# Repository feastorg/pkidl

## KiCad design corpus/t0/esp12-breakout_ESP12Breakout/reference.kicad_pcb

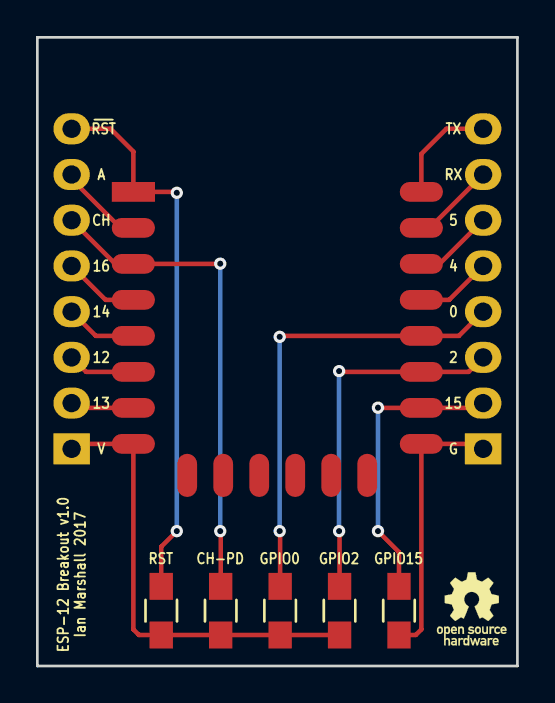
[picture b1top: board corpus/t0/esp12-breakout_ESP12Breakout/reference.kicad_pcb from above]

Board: 2 copper layers, 26.7 x 34.9 mm, 8 parts (0 on the bottom side), 16 nets.

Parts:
P1, P2: CONN_01X08; Socket_Strip_Straight_1x08
R1, R2, R3, R4, R5: 10k; R_0805_HandSoldering
U1: ESP-12E

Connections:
GND: P2.1, R5.1, U1.15
unnamed: P1.2, U1.7
unnamed: P1.3, U1.6
unnamed: P1.4, U1.5
unnamed: P1.5, U1.4
unnamed: P1.6, R2.2, U1.3
unnamed: P1.7, U1.2
unnamed: P1.8, R1.2, U1.1
unnamed: P2.2, R5.2, U1.16
unnamed: P2.3, R4.2, U1.17
unnamed: P2.4, R3.2, U1.18
unnamed: P2.5, U1.19
unnamed: P2.6, U1.20
unnamed: P2.7, U1.21
unnamed: P2.8, U1.22
VCC: P1.1, R1.1, R2.1, R3.1, R4.1, U1.8

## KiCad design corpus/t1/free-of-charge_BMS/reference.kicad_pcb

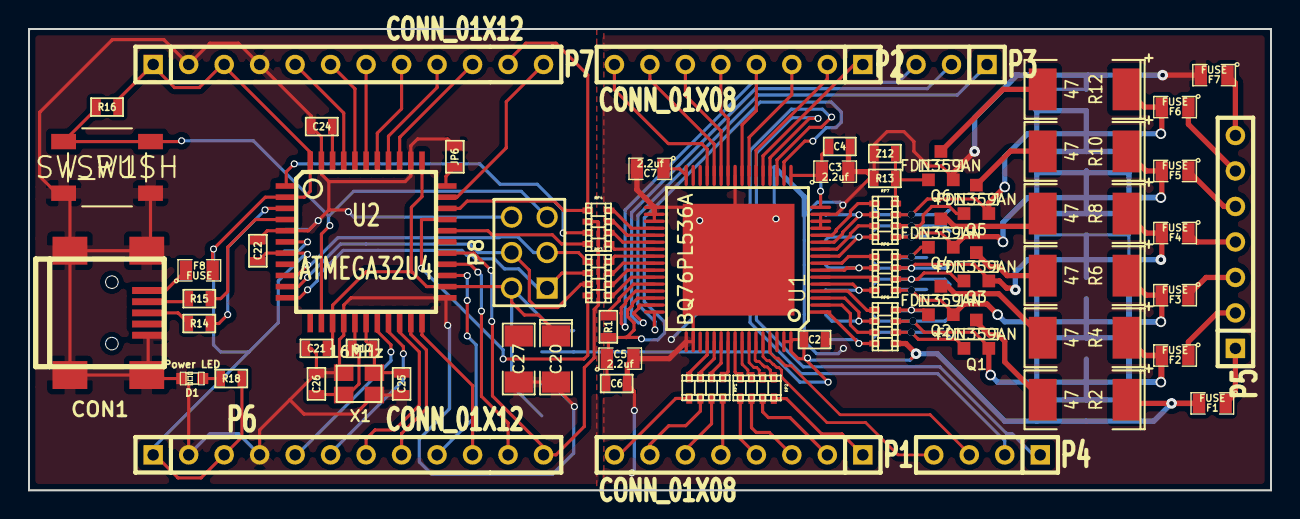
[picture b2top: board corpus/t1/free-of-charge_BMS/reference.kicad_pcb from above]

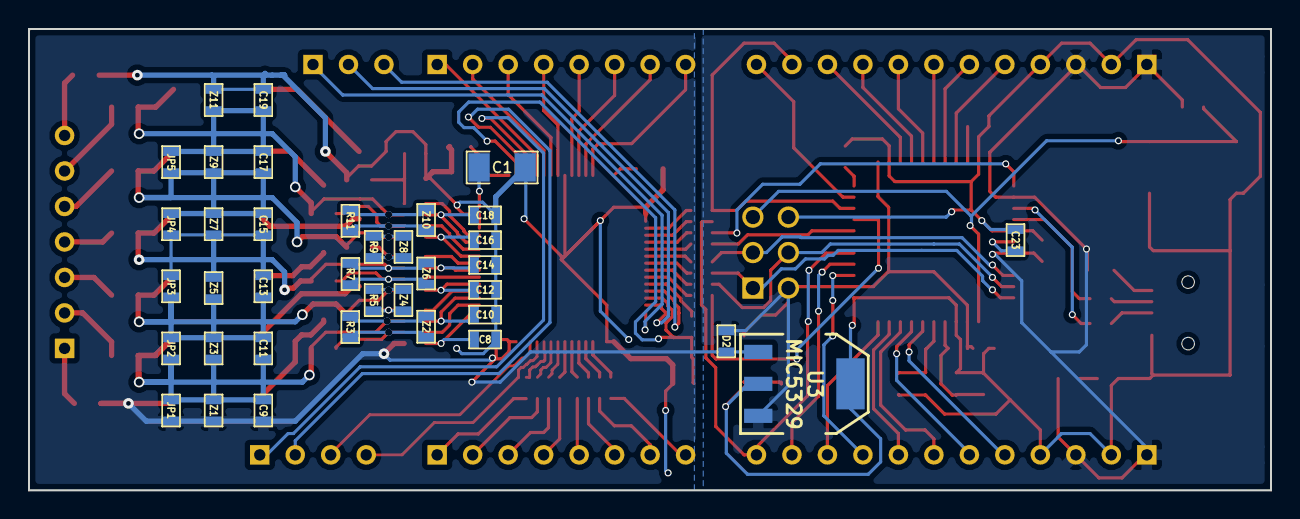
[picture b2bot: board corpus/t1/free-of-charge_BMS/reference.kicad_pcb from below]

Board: 2 copper layers, 88.9 x 33.0 mm, 100 parts (37 on the bottom side), 118 nets.

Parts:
C1, C27: 10uf; SM1206
C2, C4, C6, C8, C9, C10, C11, C12, C13, C14, C15, C16, C17, C18, C19, C21, C22, C24: 0.1uf; SM0603
C3, C5, C7: 2.2uf; SM0805
C20: 10uf; SM1206POL
C23: 1uf; SM0603
C25, C26: 20pf; SM0603
CON1: USB-MINI-B; USB_MINI_B
D1: Power LED; LED-0603
D2: DIODE; SM0603
F1, F2, F3, F4, F5, F6, F7, F8: FUSE; SM0805
JP1, JP2, JP3, JP4, JP5, JP6: JUMPER; SM0603
P1, P2: CONN_01X08; SIL-8
P3: CONN_01X03; SIL-3
P4: CONN_01X04; SIL-4
P5: CONN_01X07; SIL-7
P6, P7: CONN_01X12; SIL-12
P8: CONN_02X03; pin_array_3x2
Q1, Q2, Q3, Q4, Q5, Q6: FDN359AN; SOT23GDS
R1: 100k; SM0603
R2, R4, R6, R8, R10, R12: 47; SM2512
R3, R5, R7, R9, R11, R13: 1M 1%; SM0603
R14, R15: 22; SM0603
R16: 10k; SM0603
R17: 1M; SM0603
R18: 1k; SM0603
RP1, RP2, RP3, RP4: R_PACK4; r_cat16-4
RP5, RP6, RP7: 1k; r_cat16-4
SW1: SW_PUSH; SW
U1: BQ76PL536A; HTQFP_64
U2: ATMEGA32U4; TQFP44
U3: MIC5329; SOT223
X1: 16MHz; crystal_FA238-TSX3225
Z1, Z2, Z3, Z4, Z5, Z6, Z7, Z8, Z9, Z10, Z11, Z12: ZENER; SM0603

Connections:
+5V: C20.1, C21.1, C22.1, D2.1, F8.2, P6.1, P6.3, P7.1, P7.3, P8.2, R16.1, R18.2, U2.2, U2.7, U2.14, U2.24, U2.34, U2.44, U3.3
+BATT: C2.1, C9.1, D2.2, F1.2, JP1.1, R2.1, RP5.1, U1.63, U1.64, U3.1, Z1.2
/CellBallance/C0: F7.1, P5.7
/CellBallance/C1: F6.1, P5.6
/CellBallance/C2: F5.1, P5.5
/CellBallance/C3: F4.1, P5.4
/CellBallance/C4: F3.1, P5.3
/CellBallance/C5: F2.1, P5.2
/CellBallance/C6: F1.1, P5.1
/CellBallance/CB1: RP7.5, U1.12
/CellBallance/CB2: RP7.7, U1.10
/CellBallance/CB3: RP6.5, U1.8
/CellBallance/CB4: RP6.7, U1.6
/CellBallance/CB5: RP5.5, U1.4
/CellBallance/CB6: RP5.7, U1.2
/CellBallance/VC1: C18.2, RP7.6, U1.11
/CellBallance/VC2: C16.2, RP7.8, U1.9
/CellBallance/VC3: C14.2, RP6.6, U1.7
/CellBallance/VC4: C12.2, RP6.8, U1.5
/CellBallance/VC5: C10.2, RP5.6, U1.3
/CellBallance/VC6: C8.2, RP5.8, U1.1
/LDOA: C3.1, C4.1, U1.17
/LDOD: C5.1, C6.1, R1.2, U1.18, U1.46
/REG50: C7.1, U1.32
/VREF: C1.1, U1.16
/atmega32u4/A0: P7.10, U2.36
/atmega32u4/A1: P7.9, U2.37
/atmega32u4/A2: P7.8, U2.38
/atmega32u4/A3: P7.7, U2.39
/atmega32u4/A4: P7.6, U2.40
/atmega32u4/A5: P7.5, U2.41
/atmega32u4/ALERT_H: RP4.7, U2.1
/atmega32u4/AREF: C24.1, U2.42
/atmega32u4/CONV_H: P7.11, RP4.5, U2.31
/atmega32u4/CS_H: RP3.8, U2.30
/atmega32u4/D0/RX: P6.7, U2.20
/atmega32u4/D1/TX: P6.8, U2.21
/atmega32u4/D2/SDA: P6.6, U2.19
/atmega32u4/D3/SCL: P6.5, U2.18
/atmega32u4/D4: P6.9, U2.25
/atmega32u4/DRDY_H: P6.12, RP4.6, U2.27
/atmega32u4/FAULT_H: RP4.8, U2.29
/atmega32u4/HWB: JP6.1, U2.33
/atmega32u4/IO12: P6.11, U2.26
/atmega32u4/IO13*: P7.12, U2.32
/atmega32u4/RST: P8.5, R16.2, SW1.2, U2.13
/atmega32u4/SCLK_H: P8.3, RP3.5, U2.9
/atmega32u4/SDI_H: P8.4, RP3.7, U2.10
/atmega32u4/SDO_H: P8.1, RP3.6, U2.11
/atmega32u4/TXLED: P6.10, U2.22
/atmega32u4/UCAP: C23.1, U2.6
GND: C20.2, C21.2, C22.2, C23.2, C24.2, C25.2, C26.2, C27.2, CON1.5, CON1.6, CON1.7, CON1.8, CON1.9, D1.2, JP6.2, P6.2, P6.4, P7.2, P7.4, P8.6, SW1.1, U2.5, U2.15, U2.23, U2.35, U2.43, U3.2, U3.4, X1.3
unnamed: P2.1, U1.21
unnamed: P2.2, U1.22
unnamed: P2.3, U1.23
unnamed: P2.4, U1.24
unnamed: P2.5, U1.26
unnamed: P2.6, U1.27
unnamed: P1.3, RP2.2
unnamed: P1.2, RP2.3
unnamed: P1.1, RP2.4
unnamed: P1.4, RP2.1
unnamed: P2.7, U1.28
unnamed: P2.8, U1.29
unnamed: P1.5, RP1.4
unnamed: P1.6, RP1.3
unnamed: P1.7, RP1.2
unnamed: P1.8, RP1.1
unnamed: P3.2, U1.47
unnamed: RP1.8, U1.52
unnamed: RP1.7, U1.53
unnamed: RP1.6, U1.54
unnamed: RP1.5, U1.55
unnamed: P3.3, U1.45
unnamed: P3.1, U1.48
unnamed: P4.4, U1.60
unnamed: P4.3, U1.61
unnamed: P4.2, U1.19
unnamed: RP3.4, U1.40
unnamed: RP3.3, U1.41
unnamed: RP3.2, U1.42
unnamed: RP3.1, U1.43
unnamed: P4.1, U1.20
unnamed: RP4.4, U1.36
unnamed: RP4.3, U1.37
unnamed: RP4.2, U1.38
unnamed: RP4.1, U1.39
unnamed: RP2.8, U1.56
unnamed: RP2.7, U1.57
unnamed: RP2.6, U1.58
unnamed: RP2.5, U1.59
unnamed: R1.1, U1.44
unnamed: Q1.G, R3.1, RP5.2, Z2.2
unnamed: Q1.D, R2.2
unnamed: Q2.D, R4.2
unnamed: Q6.G, R13.1, RP7.4, Z12.2
unnamed: Q4.G, R9.1, RP6.4, Z8.2
unnamed: Q5.D, R10.2
unnamed: Q5.G, R11.1, RP7.2, Z10.2
unnamed: Q3.G, R7.1, RP6.2, Z6.2
unnamed: C13.2, C15.1, F4.2, JP3.2, JP4.1, Q3.S, R7.2, R8.1, RP6.3, Z5.1, Z6.1, Z7.2
unnamed: Q2.G, R5.1, RP5.4, Z4.2
unnamed: C15.2, C17.1, F5.2, JP4.2, JP5.1, Q4.S, R9.2, R10.1, RP7.1, Z7.1, Z8.1, Z9.2
unnamed: C17.2, C19.1, F6.2, JP5.2, Q5.S, R11.2, R12.1, RP7.3, Z9.1, Z10.1, Z11.2
unnamed: Q6.D, R12.2
unnamed: C11.2, C13.1, F3.2, JP2.2, JP3.1, Q2.S, R5.2, R6.1, RP6.1, Z3.1, Z4.1, Z5.2
unnamed: C9.2, C11.1, F2.2, JP1.2, JP2.1, Q1.S, R3.2, R4.1, RP5.3, Z1.1, Z2.1, Z3.2
unnamed: Q4.D, R8.2
unnamed: Q3.D, R6.2
unnamed: CON1.1, F8.1
unnamed: R15.2, U2.4
unnamed: R14.2, U2.3
unnamed: CON1.2, R15.1
unnamed: C26.1, R17.2, U2.16, X1.2
unnamed: C25.1, R17.1, U2.17, X1.1
unnamed: D1.1, R18.1
unnamed: CON1.3, R14.1
VSS: C1.2, C2.2, C3.2, C4.2, C5.2, C6.2, C7.2, C8.1, C10.1, C12.1, C14.1, C16.1, C18.1, C19.2, F7.2, Q6.S, R13.2, U1.0, U1.13, U1.14, U1.15, U1.25, U1.33, U1.34, U1.35, U1.49, U1.50, Z11.1, Z12.1

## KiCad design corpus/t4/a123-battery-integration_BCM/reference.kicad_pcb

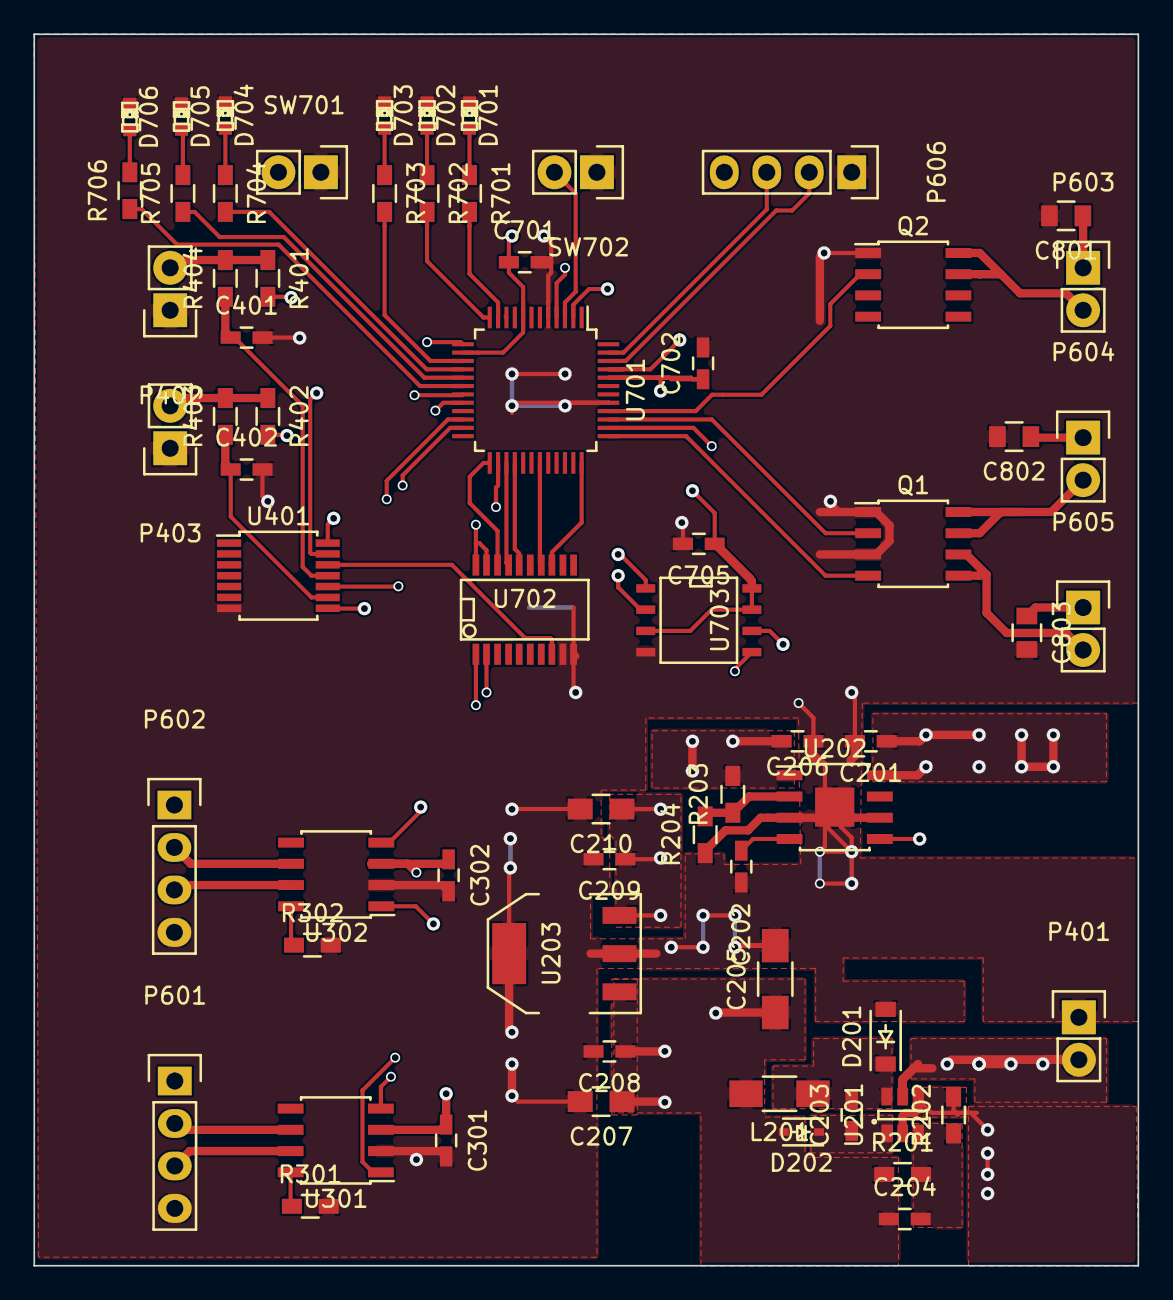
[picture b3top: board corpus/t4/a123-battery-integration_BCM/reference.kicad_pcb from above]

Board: 4 copper layers, 66.0 x 73.7 mm, 67 parts (0 on the bottom side), 59 nets.

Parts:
C201, C206, C401, C402: 1uF; C_0603_HandSoldering
C202: 10nF; C_0603_HandSoldering
C203: 0.22pF; C_0603_HandSoldering
C204: 10pF; C_0603_HandSoldering
C205: 100uF; C_1206_HandSoldering
C207, C210: 10u; C_0805_HandSoldering
C208, C209, C701, C702: 100n; C_0603_HandSoldering
C301, C302, C705: 0.1uF; C_0603_HandSoldering
C801, C802, C803: 10uF; C_0805
D201: MBR0540; SOD-123
D202: CMDSH-3; SOD-323
D701, D702, D703, D704, D705, D706: RED; LED-0603
L201: 47uH; C_1206_HandSoldering
P401: POWERCON; Pin_Header_Straight_1x02
P402: KEYSWITCH; Pin_Header_Straight_1x02
P403: CHARGESW; Pin_Header_Straight_1x02
P601: BRUSA_CANCON; Pin_Header_Straight_1x04
P602: A123_CANCON; Pin_Header_Straight_1x04
P603: CON+; Pin_Header_Straight_1x02
P604: CON-; Pin_Header_Straight_1x02
P605: CONPRE; Pin_Header_Straight_1x02
P606: UART; Pin_Header_Straight_1x04
Q1, Q2: IRF7101PbF; SOIC-8_3.9x4.9mm_Pitch1.27mm
R201: 1M; R_0603_HandSoldering
R202: 604K; R_0603_HandSoldering
R203: 88.7k; R_0603_HandSoldering
R204: 10k; R_0603_HandSoldering
R301, R302: 33k; R_0603_HandSoldering
R401, R402, R403, R404: 20k; R_0603_HandSoldering
R701, R702, R703, R704, R705, R706: 1k; R_0603_HandSoldering
SW701: ISP; Pin_Header_Straight_1x02
SW702: RESET; Pin_Header_Straight_1x02
U201: LT1934; SOT-23-6
U202: ADP7105; SOIC-8-1EP_3.9x4.9mm_Pitch1.27mm
U203: SPX2920M3-3.3; SOT-223
U301, U302: MCP2551-I/SN; SOIC-8_3.9x4.9mm_Pitch1.27mm
U401: 74LS14; TSSOP-14_4.4x5mm_Pitch0.65mm
U701: LPC11C14; LQFP-48_7x7mm_Pitch0.5mm
U702: MCP2515_TSSOP; SSOP-20
U703: AT25XX; SOIC-8-N

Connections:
+3V3: C209.1, C210.1, C701.1, C702.1, C705.1, R401.2, R402.2, U203.3, U401.14, U701.8, U701.14, U701.44, U702.19, U702.20, U703.3, U703.7, U703.8
+5V: C204.1, C205.1, C207.1, C208.1, C301.1, C302.1, D202.2, L201.2, P606.4, R201.1, U203.1, U301.3, U302.3
+12V: C206.1, P602.1, R203.1, U202.1
+15V: C201.1, C801.1, C802.1, C803.1, P401.2, P603.1, P604.1, P605.1, U201.5, U202.8
/Can transceiver/CAN1_H_I: P601.2, U301.6
/Can transceiver/CAN1_L_I: P601.3, U301.7
/Can transceiver/CAN1_RS: R301.1, U301.8
/Can transceiver/CAN1_RX: U301.4, U702.2
/Can transceiver/CAN1_TX: U301.1, U702.1
/Can transceiver/CAN2_H_I: P602.2, U302.6
/Can transceiver/CAN2_L_I: P602.3, U302.7
/Can transceiver/CAN2_RS: R302.1, U302.8
/Can transceiver/CAN2_RX: U302.4, U701.19
/Can transceiver/CAN2_TX: U302.1, U701.20
/Contactor Driver/CON+: Q2.2, U701.40
/Contactor Driver/CON+_LOW: P603.2, Q2.7, Q2.8
/Contactor Driver/CON-: Q1.2, U701.39
/Contactor Driver/CON-_LOW: P604.2, Q1.7, Q1.8
/Contactor Driver/CONPRE: Q1.4, U701.37
/Contactor Driver/CONPRE_LOW: P605.2, Q1.5, Q1.6
/Input Connectors/CHARGESWITCH_R: P403.2, R402.1, R403.2
/Input Connectors/CHARGESWITCH_RC: C402.1, R403.1, U401.9
/Input Connectors/KEYSKWITCH_RC: C401.1, R404.1, U401.11
/Input Connectors/KEYSWITCH_R: P402.2, R401.1, R404.2
/Power/5V0_BOOST: C203.1, D202.1, U201.1
/Power/5V0_FB: C204.2, R201.2, R202.1, U201.3
/Power/5V0_L: C203.2, D201.1, L201.1, U201.6
/Power/12V0_FB: R203.2, R204.1, U202.2
/Power/12V0_SS: C202.1, U202.4
/Power/EN12V0: U202.5, U701.45
/microController/CAN1_INT: U701.36, U702.13
/microController/CAN1_MISO: U701.27, U702.17
/microController/CAN1_MOSI: U701.28, U702.16
/microController/CAN1_SCK: U701.31, U702.14
/microController/CAN1_SSEL: U701.25, U702.18
/microController/CAN_OSC2: U401.12, U702.8
/microController/CHARGESWITCH_IN: U401.8, U701.22
/microController/CLKOUT: SW701.2, U401.13, U701.4
/microController/IO_LED0: R701.2, U701.11
/microController/IO_LED1: R702.2, U701.12
/microController/IO_LED2: R703.2, U701.15
/microController/IO_LED3: R704.2, U701.16
/microController/IO_LED4: R705.1, U701.17
/microController/IO_LED5: R706.1, U701.18
/microController/KEYSWITCH_IN: U401.10, U701.23
/microController/MCU_RESET: SW702.2, U701.3
/microController/MCU_RXD: P606.2, U701.46
/microController/MCU_TXD: P606.3, U701.47
/microController/PROM_MISO: U701.26, U703.2
/microController/PROM_MOSI: U701.38, U703.5
/microController/PROM_SCK: U701.13, U703.6
/microController/PROM_SSEL: U701.2, U703.1
GND: C201.2, C202.2, C205.2, C206.2, C207.2, C208.2, C209.2, C210.2, C301.2, C302.2, C401.2, C402.2, C701.2, C702.2, C705.2, C801.2, C802.2, C803.2, D201.2, D701.1, D702.1, D703.1, D704.1, D705.1, D706.1, P401.1, P402.1, P403.1, P601.4, P602.4, P606.1, Q1.1, Q1.3, Q2.1, R202.2, R204.2, R301.2, R302.2, SW701.1, SW702.1, U201.2, U201.4, U202.3, U202.6, U202.9, U203.2, U203.4, U301.2, U302.2, U401.7, U701.5, U701.41, U702.9, U702.10, U703.4
unnamed: D701.2, R701.1
unnamed: D702.2, R702.1
unnamed: D703.2, R703.1
unnamed: D704.2, R704.1
unnamed: D705.2, R705.2
unnamed: D706.2, R706.2

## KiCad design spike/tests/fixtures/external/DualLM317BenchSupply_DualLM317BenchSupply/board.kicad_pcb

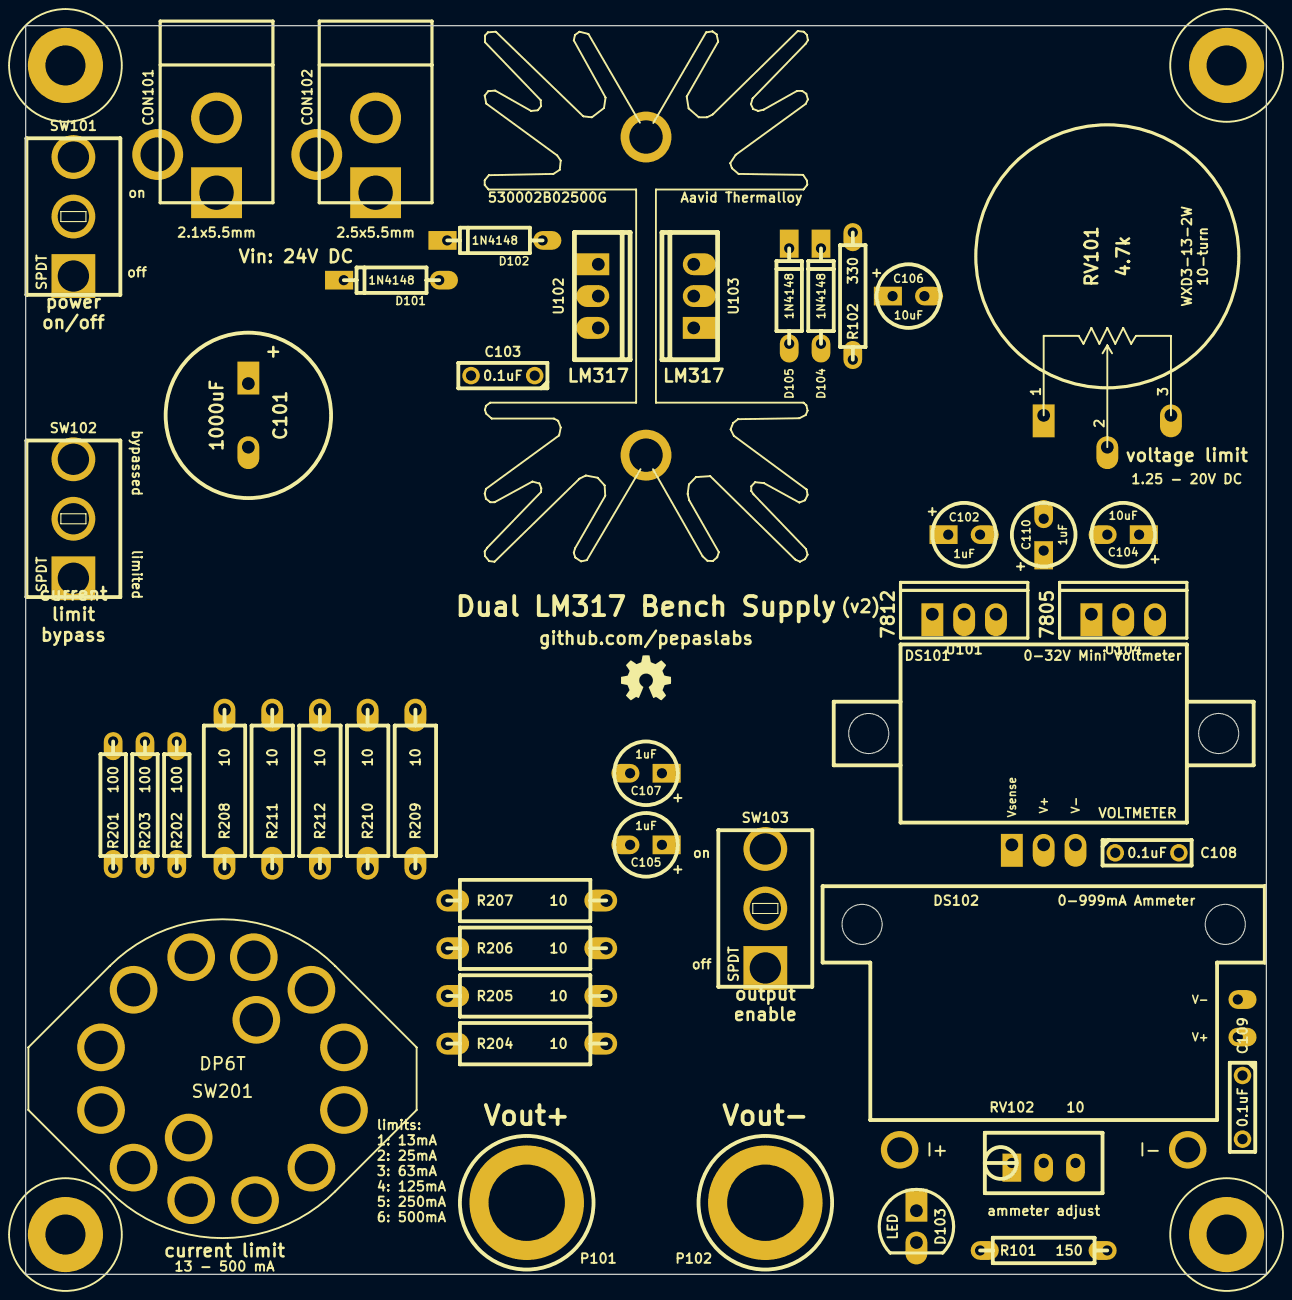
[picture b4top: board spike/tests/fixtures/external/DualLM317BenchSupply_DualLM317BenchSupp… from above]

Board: 2 copper layers, 99.1 x 99.7 mm, 50 parts (0 on the bottom side), 19 nets, no tracks yet.

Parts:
C101: 1000uF; ELCAP_20_52_V
C102, C105, C107, C110: 1uF; ELCAP_10_20_V
C103, C108, C109: 0.1uF; C2
C104, C106: 10uF; ELCAP_10_20_V
CON101: BARREL_JACK; BARREL_JACK_21x55
CON102: BARREL_JACK; BARREL_JACK_25x55
D101, D102, D104, D105: 1N4148; DIODE_3
D103: LED; LED_5MM
DS101: VOLTMETER; DVM036A
DS102: AMMETER_V; EBAY_AMMETER
H101, H102, H103, H104: HOLE; hole_M3
H***: 530002B02500G
P101: Vout+; Banana_A
P102: Vout-; Banana_A
R101: 150; R_AXIAL_0W25
R102: 330; R_AXIAL_0W25
R201, R202, R203: 100; R_AXIAL_0W25
R204, R205, R206, R207, R208, R209, R210, R211, R212: 10; R_AXIAL_0W5
RV101: 4.7k; WXD3-13-2W_A
RV102: 10; 3296W
SW101, SW102, SW103: SPDT; M2012SS1W01
SW201: DP6T; G3SR022-R
U101: 7812; TO-220_V_069B
U102, U103: LM317; TO-220_V_069B
U104: 7805; TO-220_V_069B

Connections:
5V: C104.1, C108.1, C109.1, D103.1, DS101.2, DS102.3, U104.3
12V: C110.1, U101.3, U104.1
/current_limit_r/R_LIM+: D101.1, D102.2, SW201.1, SW201.8, U102.2
/current_limit_r/R_LIM-: C105.1, D102.1, D104.2, R201.2, R202.2, R203.2, R204.2, R205.2, R206.2, R207.2, R209.2, R210.2, R211.2, R212.2, SW102.1, U102.1, U103.3
GND: C101.2, C102.2, C103.2, C104.2, C105.2, C106.2, C107.2, C108.2, C109.2, C110.2, CON101.2, CON101.3, CON102.2, CON102.3, DS101.3, DS102.2, DS102.4, R101.2, RV101.1, RV102.2, RV102.3, U101.2, U104.2
unnamed: C107.1, D104.1, D105.2, DS101.1, R102.1, SW103.2, U103.2
unnamed: C106.1, D105.1, R102.2, RV101.2, RV101.3, U103.1
unnamed: P101.1, SW103.1
unnamed: DS102.1, P102.1, RV102.1
unnamed: D103.2, R101.1
unnamed: CON101.1, CON102.1, SW101.2
unnamed: C101.1, C102.1, C103.1, D101.2, SW101.1, SW102.2, U101.1, U102.3
unnamed: R209.1, R210.1, SW201.6, SW201.13
unnamed: R204.1, R205.1, R206.1, R207.1, SW201.7, SW201.14
unnamed: R208.2, R211.1
unnamed: R212.1, SW201.5
unnamed: R208.1, SW201.4
unnamed: R201.1, SW201.2
unnamed: R202.1, R203.1, SW201.3

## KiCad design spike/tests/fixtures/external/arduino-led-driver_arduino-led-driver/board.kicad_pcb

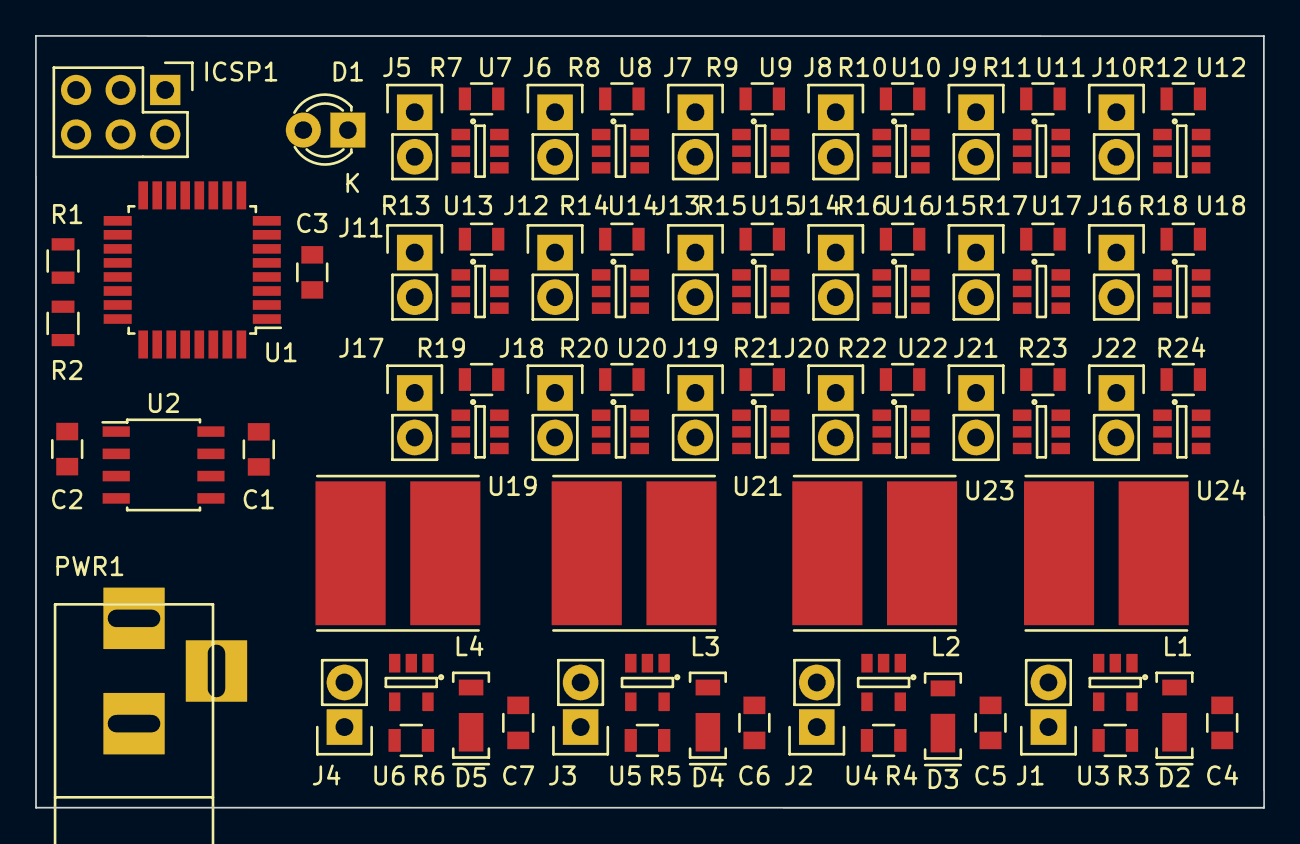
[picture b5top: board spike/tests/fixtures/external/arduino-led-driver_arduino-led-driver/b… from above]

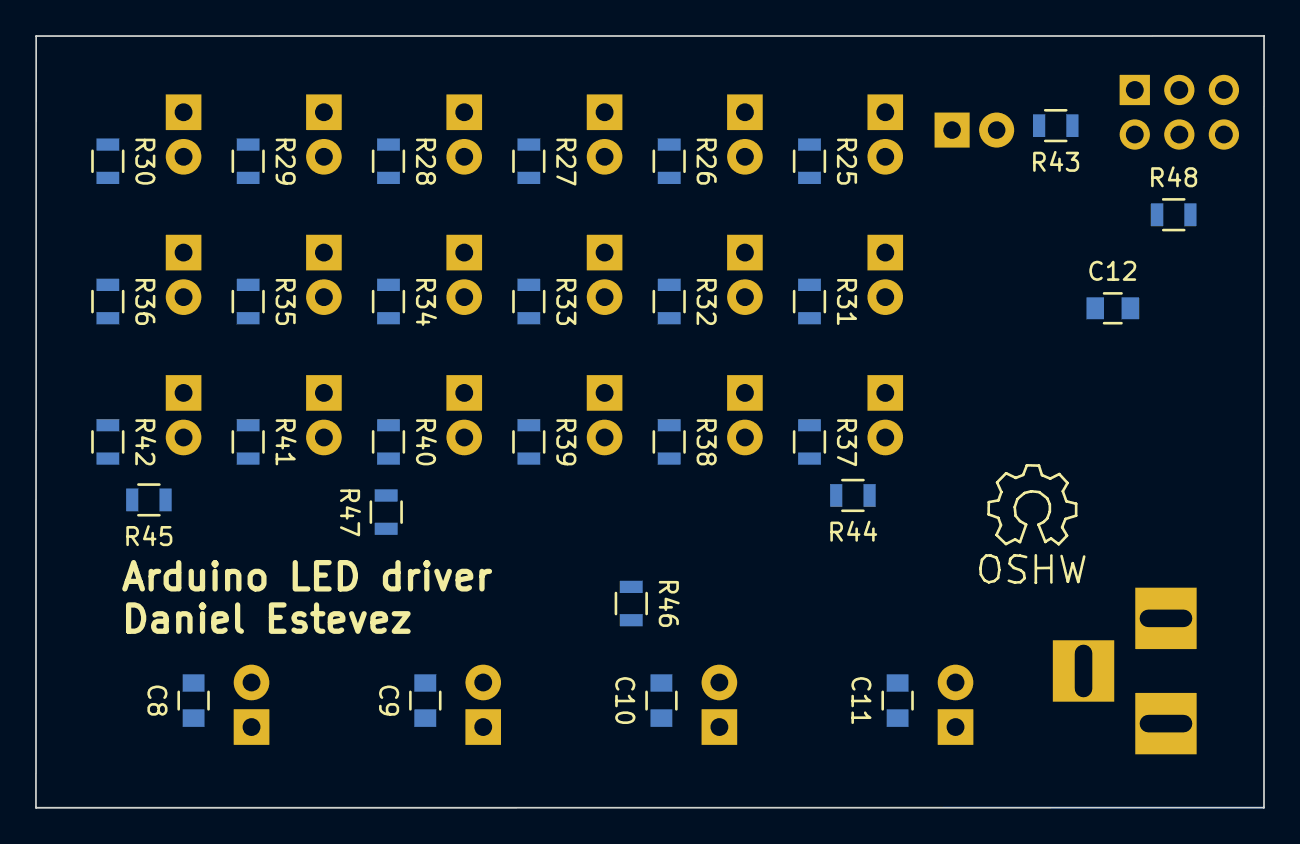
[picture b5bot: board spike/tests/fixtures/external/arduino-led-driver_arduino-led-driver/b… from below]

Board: 2 copper layers, 70.0 x 44.0 mm, 118 parts (30 on the bottom side), 77 nets, no tracks yet.

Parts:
C1: 330n; C_0805
C2, C3, C12: 100n; C_0805
C4, C5, C6, C7: 2.2u; C_0805
C8, C9, C10, C11: 1u; C_0805
D1: LED; LED-3MM
D2, D3, D4, D5: DFLS240L; POWERDI-123
ICSP1: AVR-ISP-6; Pin_Header_Straight_2x03
J1, J2, J3, J4, J5, J6, J7, J8, J9, J10, J11, J12, J13, J14, J15, J16, J17, J18, J19, J20, J21, J22: CONN_01X02; Socket_Strip_Straight_1x02
L1, L2, L3, L4: 33u; VLP8040
Noname_1: Symbol_OSHW-Logo_SilkScreen
PWR1: BARREL_JACK
R1, R2, R7, R8, R9, R10, R11, R12, R13, R14, R15, R16, R17, R18, R19, R20, R21, R22, R23, R24, R25, R26, R27, R28, R29, R30, R31, R32, R33, R34, R35, R36, R37, R38, R39, R40, R41, R42: 100K; R_0805
R3, R4, R5, R6: 130m; R_0805
R43: 10K; R_0805
R44, R45, R46, R47: 2.2K; R_0805
R48: 10k; R_0805
U1: ATMEGA328P-A; TQFP-32_7x7mm_Pitch0.8mm
U2: L78L05ACD; SOIC-8_3.9x4.9mm_Pitch1.27mm
U3, U4, U5, U6: AL8808; SOT-23-5
U7, U8, U9, U10, U11, U12, U13, U14, U15, U16, U17, U18, U19, U20, U21, U22, U23, U24: BCR420UW6; SOT-23-6

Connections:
+5V: C2.1, C3.1, ICSP1.2, R43.1, R48.1, U1.4, U1.6, U1.18, U2.1
+12V: C1.1, C4.1, C5.1, C6.1, C7.1, D2.1, D3.1, D4.1, D5.1, J5.1, J6.1, J7.1, J8.1, J9.1, J10.1, J11.1, J12.1, J13.1, J14.1, J15.1, J16.1, J17.1, J18.1, J19.1, J20.1, J21.1, J22.1, PWR1.1, R3.2, R4.2, R5.2, R6.2, U2.8, U3.5, U4.5, U5.5, U6.5
EN1: R7.1, U1.12, U7.1
EN2: ICSP1.4, R8.1, U1.15, U8.1
EN3: ICSP1.1, R9.1, U1.16, U9.1
EN4: ICSP1.3, R10.1, U1.17, U10.1
EN5: R11.1, U1.7, U11.1
EN6: R12.1, U1.8, U12.1
EN7: R13.1, U1.23, U13.1
EN8: R14.1, U1.24, U14.1
EN9: R15.1, U1.25, U15.1
EN10: R16.1, U1.26, U16.1
EN11: R17.1, U1.27, U17.1
EN12: R18.1, U1.28, U18.1
EN13: R19.1, U1.30, U19.1
EN14: R20.1, U1.31, U20.1
EN15: R21.1, U1.32, U21.1
EN16: R22.1, U1.1, U22.1
EN17: R23.1, U1.2, U23.1
EN18: R24.1, U1.11, U24.1
GND: C1.2, C2.2, C3.2, C4.2, C5.2, C6.2, C7.2, C12.2, D1.1, ICSP1.6, PWR1.2, PWR1.3, R1.2, R2.2, R7.2, R8.2, R9.2, R10.2, R11.2, R12.2, R13.2, R14.2, R15.2, R16.2, R17.2, R18.2, R19.2, R21.2, R22.2, R23.2, R24.2, R25.2, R26.2, R27.2, R28.2, R29.2, R30.2, R31.2, R32.2, R33.2, R34.2, R35.2, R36.2, R37.2, R38.2, R39.2, R40.2, R41.2, R42.2, R44.2, R45.2, R46.2, R47.2, U1.3, U1.5, U1.21, U2.2, U2.3, U2.6, U2.7, U3.2, U4.2, U5.2, U6.2, U7.4, U8.4, U9.4, U10.4, U11.4, U12.4, U13.4, U14.4, U15.4, U16.4, U17.4, U18.4, U19.4, U20.4, U21.4, U22.4, U23.4, U24.4
unnamed: C8.1, J1.1, R3.1, U3.4
unnamed: C8.2, J1.2, L1.1
unnamed: C9.1, J2.1, R4.1, U4.4
unnamed: C9.2, J2.2, L2.1
unnamed: C10.1, J3.1, R5.1, U5.4
unnamed: C10.2, J3.2, L3.1
unnamed: C11.1, J4.1, R6.1, U6.4
unnamed: C11.2, J4.2, L4.1
unnamed: C12.1, ICSP1.5, R48.2, U1.29
unnamed: D1.2, R43.2
unnamed: D2.2, L1.2, U3.1
unnamed: D3.2, L2.2, U4.1
unnamed: D4.2, L3.2, U5.1
unnamed: D5.2, L4.2, U6.1
unnamed: J5.2, U7.2, U7.3, U7.5
unnamed: J6.2, U8.2, U8.3, U8.5
unnamed: J7.2, U9.2, U9.3, U9.5
unnamed: J8.2, U10.2, U10.3, U10.5
unnamed: J9.2, U11.2, U11.3, U11.5
unnamed: J10.2, U12.2, U12.3, U12.5
unnamed: J11.2, U13.2, U13.3, U13.5
unnamed: J12.2, U14.2, U14.3, U14.5
unnamed: J13.2, U15.2, U15.3, U15.5
unnamed: J14.2, U16.2, U16.3, U16.5
unnamed: J15.2, U17.2, U17.3, U17.5
unnamed: J16.2, U18.2, U18.3, U18.5
unnamed: J17.2, U19.2, U19.3, U19.5
unnamed: J18.2, U20.2, U20.3, U20.5
unnamed: J19.2, U21.2, U21.3, U21.5
unnamed: J20.2, U22.2, U22.3, U22.5
unnamed: J21.2, U23.2, U23.3, U23.5
unnamed: J22.2, U24.2, U24.3, U24.5
unnamed: R1.1, U1.19
unnamed: R2.1, U1.22
unnamed: R25.1, U7.6
unnamed: R26.1, U8.6
unnamed: R27.1, U9.6
unnamed: R28.1, U10.6
unnamed: R29.1, U11.6
unnamed: R30.1, U12.6
unnamed: R31.1, U13.6
unnamed: R32.1, U14.6
unnamed: R33.1, U15.6
unnamed: R34.1, U16.6
unnamed: R35.1, U17.6
unnamed: R36.1, U18.6
unnamed: R37.1, U19.6
unnamed: R38.1, U20.6
unnamed: R39.1, U21.6
unnamed: R40.1, U22.6
unnamed: R41.1, U23.6
unnamed: R42.1, U24.6
unnamed: R44.1, U1.9, U6.3
unnamed: R45.1, U1.13, U3.3
unnamed: R46.1, U1.10, U5.3
unnamed: R47.1, U1.14, U4.3

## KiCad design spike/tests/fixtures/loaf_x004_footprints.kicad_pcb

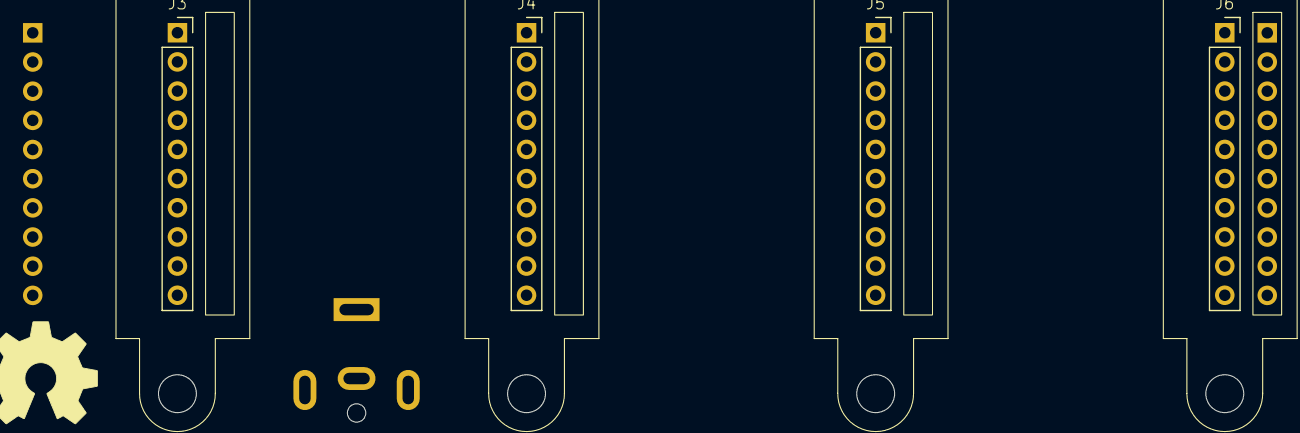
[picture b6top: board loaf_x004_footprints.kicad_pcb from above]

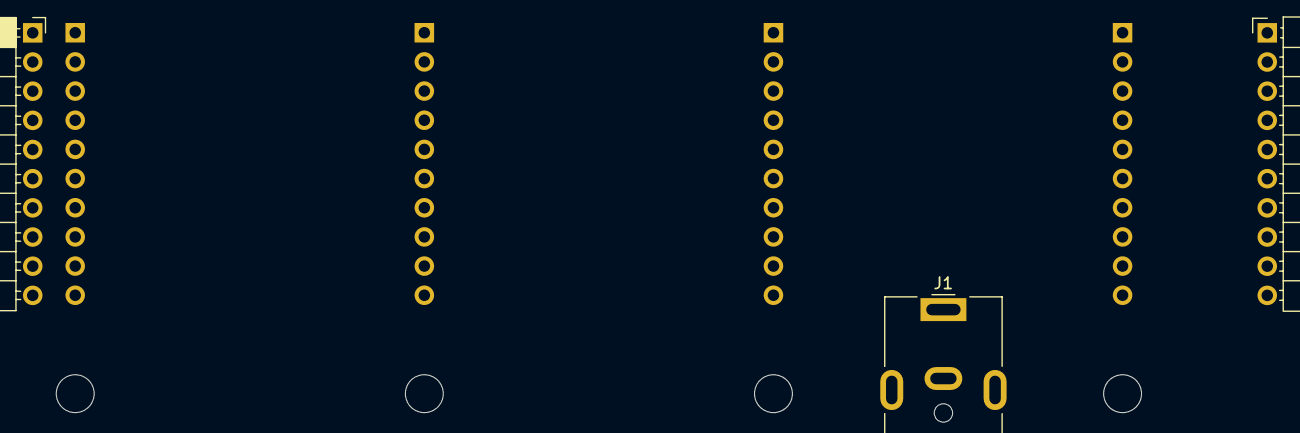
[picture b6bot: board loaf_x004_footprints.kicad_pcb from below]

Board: 0 copper layers, 8 parts (3 on the bottom side), 7 nets, no tracks yet.

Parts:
J1: Barrel_Jack; BarrelJack_CUI_PJ-063AH_Horizontal
J2: Conn_01x10_Pin; PinHeader_1x10_P2.54mm_Horizontal
J3, J4, J5, J6: Conn_01x10_Pin; BREAD_Slice_Bus_10Pin
J7: Conn_01x10_Socket; PinSocket_1x10_P2.54mm_Horizontal
Ref**: Val**; OSHW_Logo_10mm

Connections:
+12V: J1.1, J2.2, J2.9, J3.2, J3.9, J4.2, J4.9, J5.2, J5.9, J6.2, J6.9, J7.2, J7.9
/E_STOP_5V: J2.6, J3.6, J4.6, J5.6, J6.6, J7.6
/INT_5V: J2.7, J3.7, J4.7, J5.7, J6.7, J7.7
/SCL_5V: J2.3, J3.3, J4.3, J5.3, J6.3, J7.3
/SDA_5V: J2.4, J3.4, J4.4, J5.4, J6.4, J7.4
/SYNC_5V: J2.8, J3.8, J4.8, J5.8, J6.8, J7.8
GND: J1.2, J2.1, J2.5, J2.10, J3.1, J3.5, J3.10, J4.1, J4.5, J4.10, J5.1, J5.5, J5.10, J6.1, J6.5, J6.10, J7.1, J7.5, J7.10

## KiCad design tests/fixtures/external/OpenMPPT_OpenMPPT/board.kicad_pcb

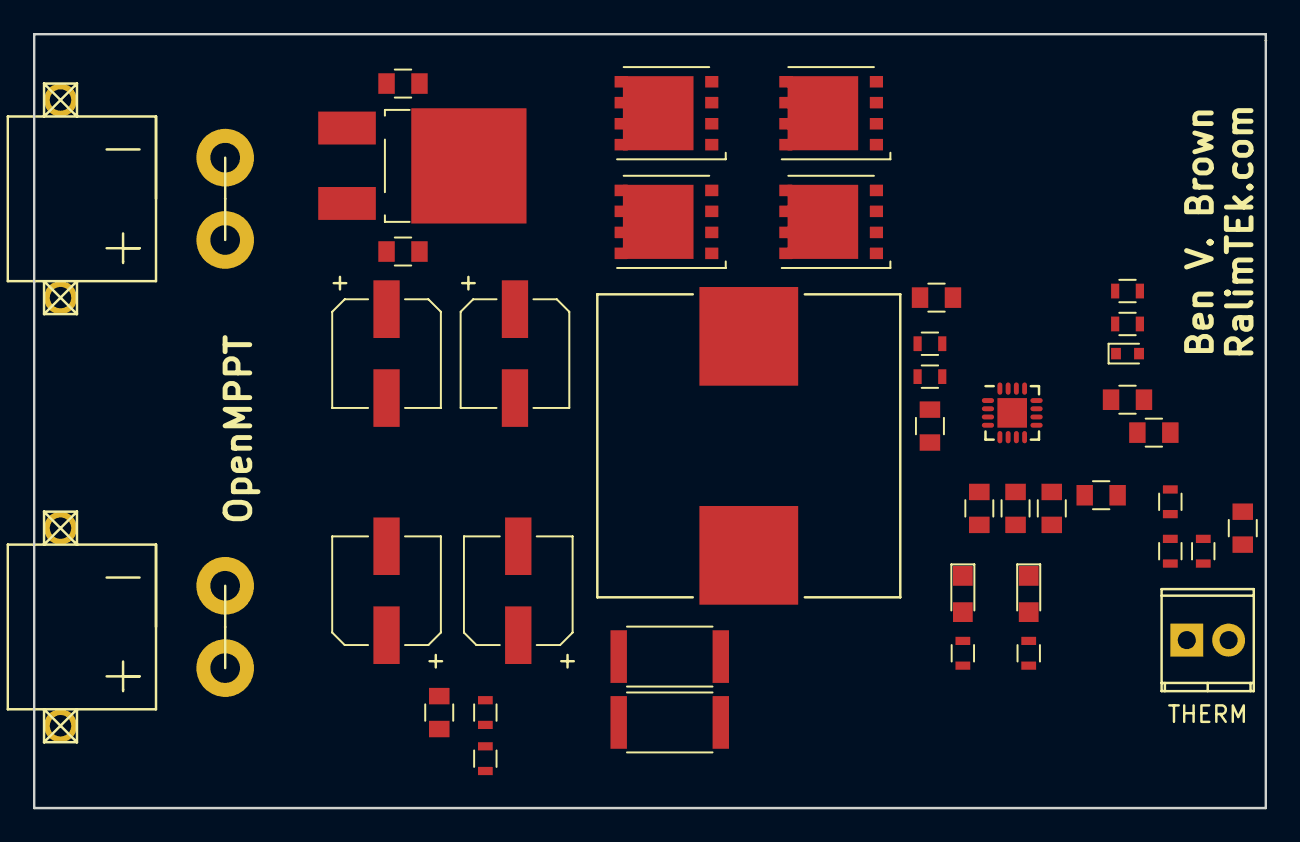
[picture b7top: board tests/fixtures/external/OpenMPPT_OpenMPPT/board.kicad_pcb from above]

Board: 2 copper layers, 74.8 x 47.0 mm, 42 parts (0 on the bottom side), 19 nets, no tracks yet.

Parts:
C101: -; C_0805
C102, C103, C106, C107, C110, C115: 1.0uF; C_0805
C104, C105, C109, C112, C113: 0.1uF; C_0805
C108, C111, C114, C116: CP; CP_Elec_6.3x7.7
D101: MBRD10100CT; TO-252-2_Rectifier
D102: D_Schottky; D_SOD-523
D103, D104: LED; LED_0805
J101: THERM; TerminalBlock_Pheonix_MPT-2.54mm_2pol
J103, J104: XT60; XT30PW_Male
L101: 3.3uH; Inductor_Wurth_HCI-1890
Q101, Q102, Q103, Q104: FDMS8050; TDSON-8-1
R101: 10k; R_0603
R102, R108, R109: 5.23k; R_0603
R103: 30.1k; R_0603
R105: -; R_0603
R106: 10; R_0603
R110, R113: 0.01; R_2512
R111, R114: 499k; R_0603
R112: 100k; R_0603
R115: 36k; R_0603
U101: BQ24650; QFN-16-1EP_3x3mm_Pitch0.5mm

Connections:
/HIGH_DRIVE: Q101.4, Q103.4, U101.15
/LOW_DRIVE: Q102.4, Q104.4, U101.13
/MPPTSET: R114.2, R115.1, U101.2
/STAT1: D103.1, U101.3
/STAT2: D104.1, U101.5
/VREF: C103.1, R102.1, R108.1, R109.1, U101.6, U101.7
GND: C101.2, C102.1, C103.2, C104.2, C106.2, C107.2, C108.2, C110.2, C111.2, C113.1, C114.2, C115.2, C116.2, J101.2, J103.2, J104.2, Q102.1, Q102.2, Q102.3, Q104.1, Q104.2, Q104.3, R101.2, R103.2, R112.2, R115.2, U101.11, U101.17
unnamed: C101.1, J101.1, R101.1, R102.2, R103.1, U101.4
unnamed: C102.2, R105.2, R106.2, U101.1
unnamed: C104.1, C107.1, D102.2, U101.12
unnamed: C105.1, L101.1, Q101.1, Q101.2, Q101.3, Q102.5, Q103.1, Q103.2, Q103.3, Q104.5, U101.14
unnamed: C105.2, D102.1, U101.16
unnamed: C106.1, C108.1, C114.1, C115.1, D101.2, Q101.5, Q103.5, R105.1, R106.1
unnamed: C109.1, C110.1, C111.1, C112.2, C116.1, J104.1, R110.1, R111.1, R113.2, U101.9
unnamed: C109.2, L101.2, R110.2, R113.1, U101.10
unnamed: C112.1, C113.2, R111.2, R112.1, U101.8
unnamed: D101.1, D101.3, J103.1, R114.1
unnamed: D103.2, R108.2
unnamed: D104.2, R109.2
